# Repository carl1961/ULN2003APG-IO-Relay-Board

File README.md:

# ULN2003APG-IO-Relay-Board
Module board utilizing all 7 ports of ULN2003APG,

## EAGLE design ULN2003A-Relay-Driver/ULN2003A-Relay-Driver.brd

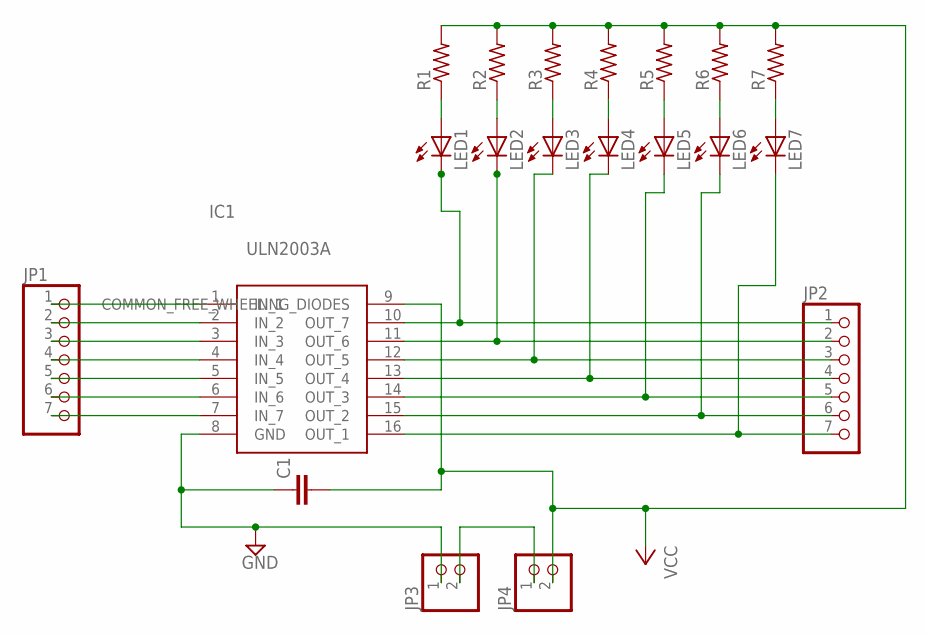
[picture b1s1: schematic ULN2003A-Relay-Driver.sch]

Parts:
C1: C5/5; C5B5
IC1: ULN2003A; DIP794W56P254L1888H533Q16N
JP1, JP2: PINHD-1X7; 1X07
JP3, JP4: PINHD-1X2; 1X02
LED1, LED2, LED3, LED4, LED5, LED6, LED7: LED3MM
R1, R2, R3, R4, R5, R6, R7: R-US_0204/7; 0204/7

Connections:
GND: C1.1, IC1.8 (GND), JP3.1
unnamed: IC1.1 (IN_1), JP1.1
unnamed: IC1.2 (IN_2), JP1.2
unnamed: IC1.3 (IN_3), JP1.3
unnamed: IC1.4 (IN_4), JP1.4
unnamed: IC1.5 (IN_5), JP1.5
unnamed: IC1.6 (IN_6), JP1.6
unnamed: IC1.7 (IN_7), JP1.7
unnamed: IC1.16 (OUT_1), JP2.7, LED7.K (C)
unnamed: IC1.14 (OUT_3), JP2.5, LED5.K (C)
unnamed: IC1.13 (OUT_4), JP2.4, LED4.K (C)
unnamed: IC1.12 (OUT_5), JP2.3, LED3.K (C)
unnamed: IC1.11 (OUT_6), JP2.2, LED2.K (C)
unnamed: IC1.10 (OUT_7), JP2.1, LED1.K (C)
unnamed: JP3.2, JP4.1
unnamed: LED1.A, R1.1
unnamed: LED2.A, R2.1
unnamed: LED3.A, R3.1
unnamed: LED4.A, R4.1
unnamed: LED5.A, R5.1
unnamed: LED6.A, R6.1
unnamed: LED7.A, R7.1
unnamed: IC1.15 (OUT_2), JP2.6, LED6.K (C)
VCC: C1.2, IC1.9 (COMMON_FREE_WHEELING_DIODES), JP4.2, R1.2, R2.2, R3.2, R4.2, R5.2, R6.2, R7.2

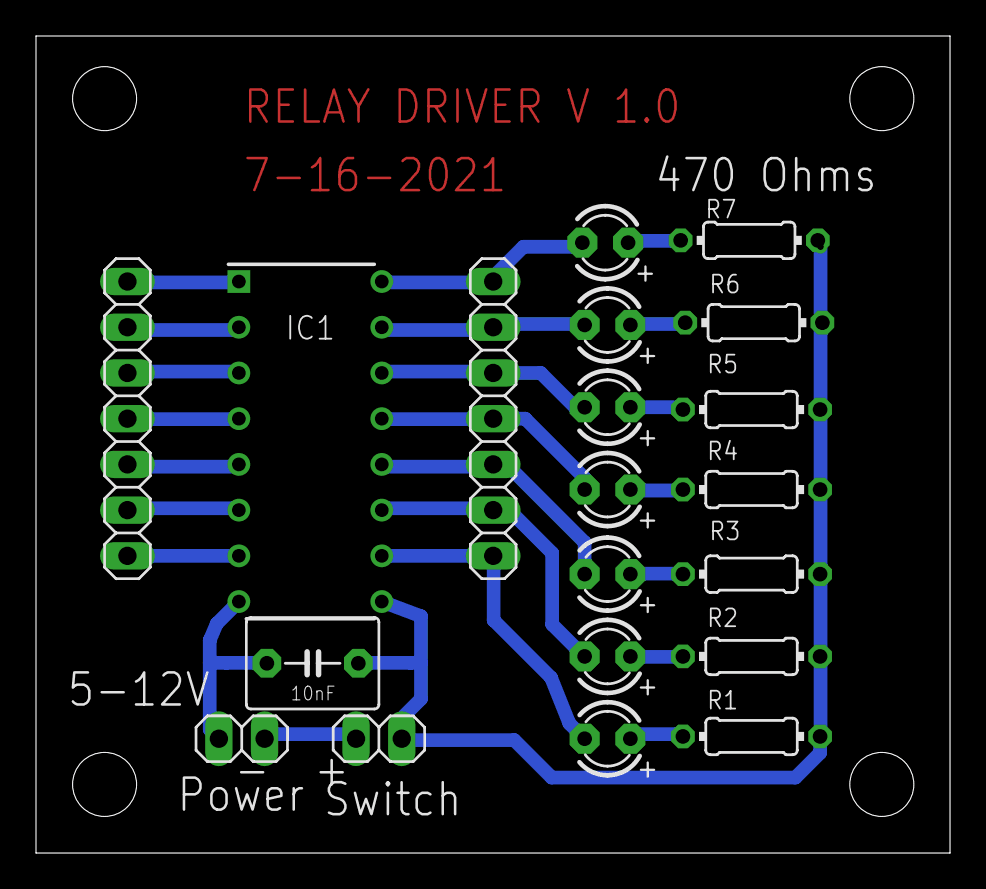
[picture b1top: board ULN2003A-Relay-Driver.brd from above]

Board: 2 copper layers, 50.8 x 45.4 mm, 20 parts (0 on the bottom side), 24 nets.

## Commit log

2021-08-01 Uploaded
    Eagle Files
